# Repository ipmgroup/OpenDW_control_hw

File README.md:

# 🌊 OpenDW Control Hardware

Control PCB for the [Open Deep Water](https://github.com/ipmgroup/Open_Deep_Water) project - an open platform for collecting, analyzing, and publishing oceanographic, climate, and environmental data.

## 📋 Overview

This PCB is a HAT module (Hardware Attached on Top) for Raspberry Pi, designed for integration with HiFiBerry DAC+ ADC and providing control for various OEM-WetEnd devices within the Open Deep Water ecosystem.

## 🔧 Key Features

- **Raspberry Pi Compatibility**: Standard 40-pin GPIO connector
- **HiFiBerry DAC+ ADC Integration**: Support for high-quality audio input/output
- **Analog-to-Digital Conversion**: Analog_to_PWM module for analog signal processing
- **Power System**: Specialized power supply for stable operation
- **Modular Architecture**: Division into functional blocks for simplified development

## 🏗️ Architecture

### Functional Blocks:

1. **Main Module (Root)**
   - Raspberry Pi interface
   - HiFiBerry DAC+ ADC connection
   - System connections

2. **Analog-to-Digital Conversion Module (U_PWM)**
   - Analog signal conversion
   - PWM generation
   - Sensor interface

3. **Power Module (U_Power)**
   - Voltage stabilization
   - Power filtering
   - Overvoltage protection

## 🔌 HiFiBerry DAC+ ADC Compatibility

The board is designed to work in conjunction with HiFiBerry DAC+ ADC, providing:
- High-quality audio playback (DAC)
- Low-noise audio recording (ADC)
- I2S interface for digital audio
- Shared Raspberry Pi GPIO usage

## 🚀 Quick Start

### 1. Repository Cloning
```bash
git clone https://github.com/ipmgroup/OpenDW_control_hw.git
cd OpenDW_control_hw
```

## 🔬 Open Deep Water Integration

This board is part of the Open Deep Water ecosystem and provides:

- **HAT Adapter**: Connection of various OEM-WetEnd devices
- **NAT Support**: Hardware foundation for software protocol adapters
- **Data Collection**: Interfaces for oceanographic sensors

## 🤝 Contributing

We welcome community participation in project development:

### For Equipment Manufacturers:
- Providing OEM-WetEnd device specifications
- Compatibility testing
- Development of specialized adapters

### For Researchers:
- Defining sensor interface requirements
- Field testing
- Functionality feedback

## 📜 License

- **Hardware**: CERN Open Hardware License v2
- **Documentation**: Creative Commons CC-BY 4.0

## 📞 Contact

- **Author**: Andrew Buckin (AB)
- **Organization**: © IPM Group
- **Email**: ipm.grp@googlemail.com
- **Project**: [Open Deep Water](https://github.com/ipmgroup/Open_Deep_Water)
- **Document Version**: 0.1
- **Date**: 08.09.2025

## 🌊 Mission

> Opening the depths of scientific collaboration through open hardware, open data, and open science.

---

**Note**: The project is in the concept stage, formation of the development team and partners is underway.

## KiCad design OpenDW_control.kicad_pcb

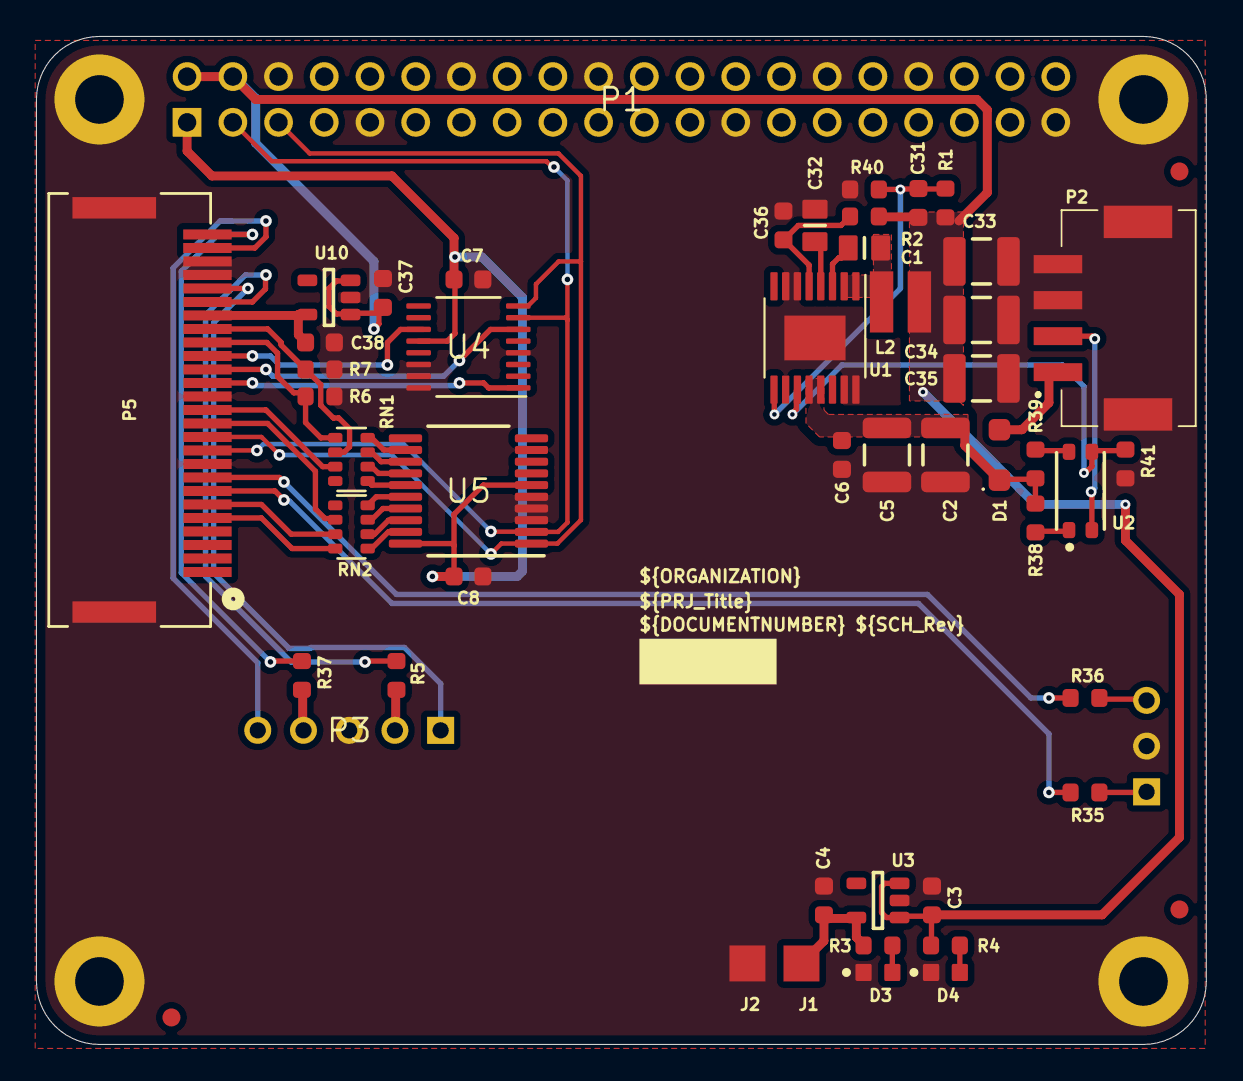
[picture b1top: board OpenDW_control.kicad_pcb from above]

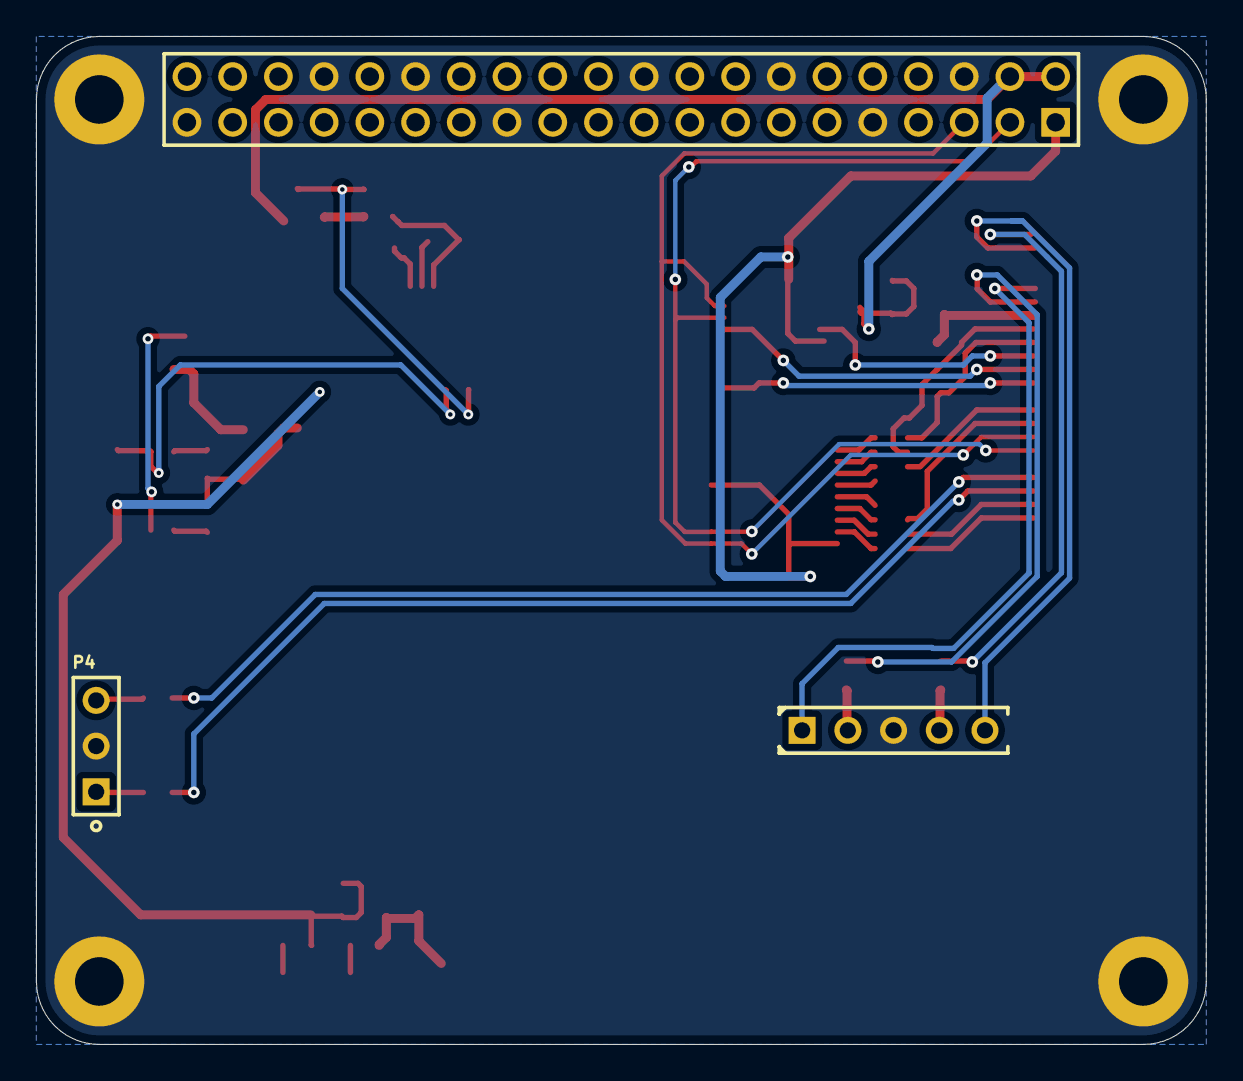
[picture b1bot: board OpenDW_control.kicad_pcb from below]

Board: 2 copper layers, 65.0 x 56.0 mm, 56 parts (3 on the bottom side), 47 nets.

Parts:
B1, B2, B3, B4: MTG270_500
C1: 0.47µF; CAPC2012X135N
C2, C5: 10µF; CAPC3225X140N
C3, C4, C37, C38: 1µF; CAPC1608X87N
C6: 1800pF; CAPC1608X87N
C7, C8: CAPC1608X87N
C31: 120pF; CAPC1608X87N
C32: 3.3µF; CAPC2012X135N
C33, C34, C35: 22µF; CAPC3225X250N
C36: 0.1µF; CAPC1608X87N
D1: TSSW3U45 RVG; SOD-123W
D3, D4: Green; LEDC1608X80N G
FTG1, FTG2, FTG3: FIDUCIAL_TOP_C100-200
J1, J2: 2 way net tie junction; J_pin_2x2
L2: 2.2 µH; WE-MAIA_3020
P1: M20-6102045_RPI
P2: 5024940470; MOLEX_5024940470
P3: HDR1X5 75915-405LF
P4: 0901471103; HDR1X3 0901471103
P5: CONN_503148_26_MOL
R1: 100k; RESC1608X55N
R2: 3.01 ohm; RESC1608X55N
R3: 1k5; RESC1608X55N
R4: 5k1; RESC1608X55N
R5, R6, R7: RESC1608X55N
R35, R36, R37: 0 ohm; RESC1608X55N
R38: 10k; RESC1608X55N
R39: 47k; RESC1608X55N
R40: 29k4; RESC1608X55N
R41: 15k; RESC1608X55N
RN1, RN2: EXB-V8V470JV; CAC-80P320X160-8N
U1: LM53602AQPWPTQ1; SOP65P640X120-17N
U2: PS2911-1-F3-AX; PANASONIC_AQY22(SSOP)
U3, U10: TPS70633DBVR; DBV0005A_N
U4: PW16-L
U5: MCP23008-E/SS; SOP65P780X200-20N

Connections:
3A3: C4.2, J1.1, R3.2, U3.5
3D3: C7.2, C8.2, P1.1, U4.12, U5.6, U5.20
3O3: C38.2, P5.20, U10.5
5V: C3.2, C31.2, C33.2, C34.2, C35.2, C37.2, L2.2, P1.2, P1.4, R1.2, R2.2, R4.2, U3.1, U3.3, U10.1, U10.3
A_IN1+: P3.1, P5.22
A_IN1-: P5.21, R5.1
A_IN2+: P3.5, P5.25
A_IN2-: P5.26, R37.1
A_OUT+: P5.7, R35.2
A_OUT-: P5.8, R36.2
BIAS: C36.2, R2.1, U1.5
CLK: P5.17, U4.11
EN: R41.2, U1.11, U2.3
FB: C31.1, R1.1, R40.2, U1.9
GND: B1.1, B2.1, B3.1, B4.1, C2.1, C3.1, C4.1, C5.1, C6.1, C7.1, C8.1, C32.1, C33.1, C34.1, C35.1, C36.1, C37.1, C38.1, D3.1, D4.1, J2.1, P1.6, P1.9, P1.14, P1.20, P1.25, P1.30, P1.34, P1.39, P2.3, P2.4, P2.P1, P2.P2, P3.3, P4.2, P5.9, P5.14, P5.23, P5.24, P5.S1, P5.S2, R6.1, R7.1, R40.1, R41.1, U1.6, U1.7, U1.10, U1.15, U1.16, U1.17, U3.2, U4.4, U4.14, U4.15, U4.16, U5.3, U5.4, U5.5, U5.9, U10.2
IO0: P5.18, R6.2, RN1.1
IO1: P5.19, R7.2, RN1.2
IO2: P5.13, RN1.3
IO5: P5.12, RN2.2
IO6: P5.6, RN2.3
IO7: P5.5, RN2.4
MOSI: P5.16, U4.6
NetC1_2: C1.2, U1.3
NetC32_2: C32.2, U1.4
NetD3_2: D3.2, R3.1
NetD4_2: D4.2, R4.1
NetP3_2: P3.2, R5.2
NetP3_4: P3.4, R37.2
NetP4_1: P4.1, R35.1
NetP4_3: P4.3, R36.1
NetR38_1: R38.1, U2.1
NetR39_1: R39.1, U2.4
NetRN1_5: RN1.5, U5.15
NetRN1_6: RN1.6, U5.14
NetRN1_7: RN1.7, U5.13
NetRN1_8: RN1.8, U5.12
NetRN2_5: RN2.5, U5.19
NetRN2_6: RN2.6, U5.18
NetRN2_7: RN2.7, U5.17
NetRN2_8: RN2.8, U5.16
Power_ON: P2.2, U2.2
SCL: P1.5, P5.11, U4.8, U5.1
SDA: P1.3, P5.10, U4.7, U5.2
SW: C1.1, L2.1, U1.1, U1.2
VPP: D1.2, P2.1
Vin: C2.2, C5.2, C6.2, D1.1, R38.2, R39.2, U1.12, U1.13
nCS: P5.15, U4.1

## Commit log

2025-09-08 add README.md
